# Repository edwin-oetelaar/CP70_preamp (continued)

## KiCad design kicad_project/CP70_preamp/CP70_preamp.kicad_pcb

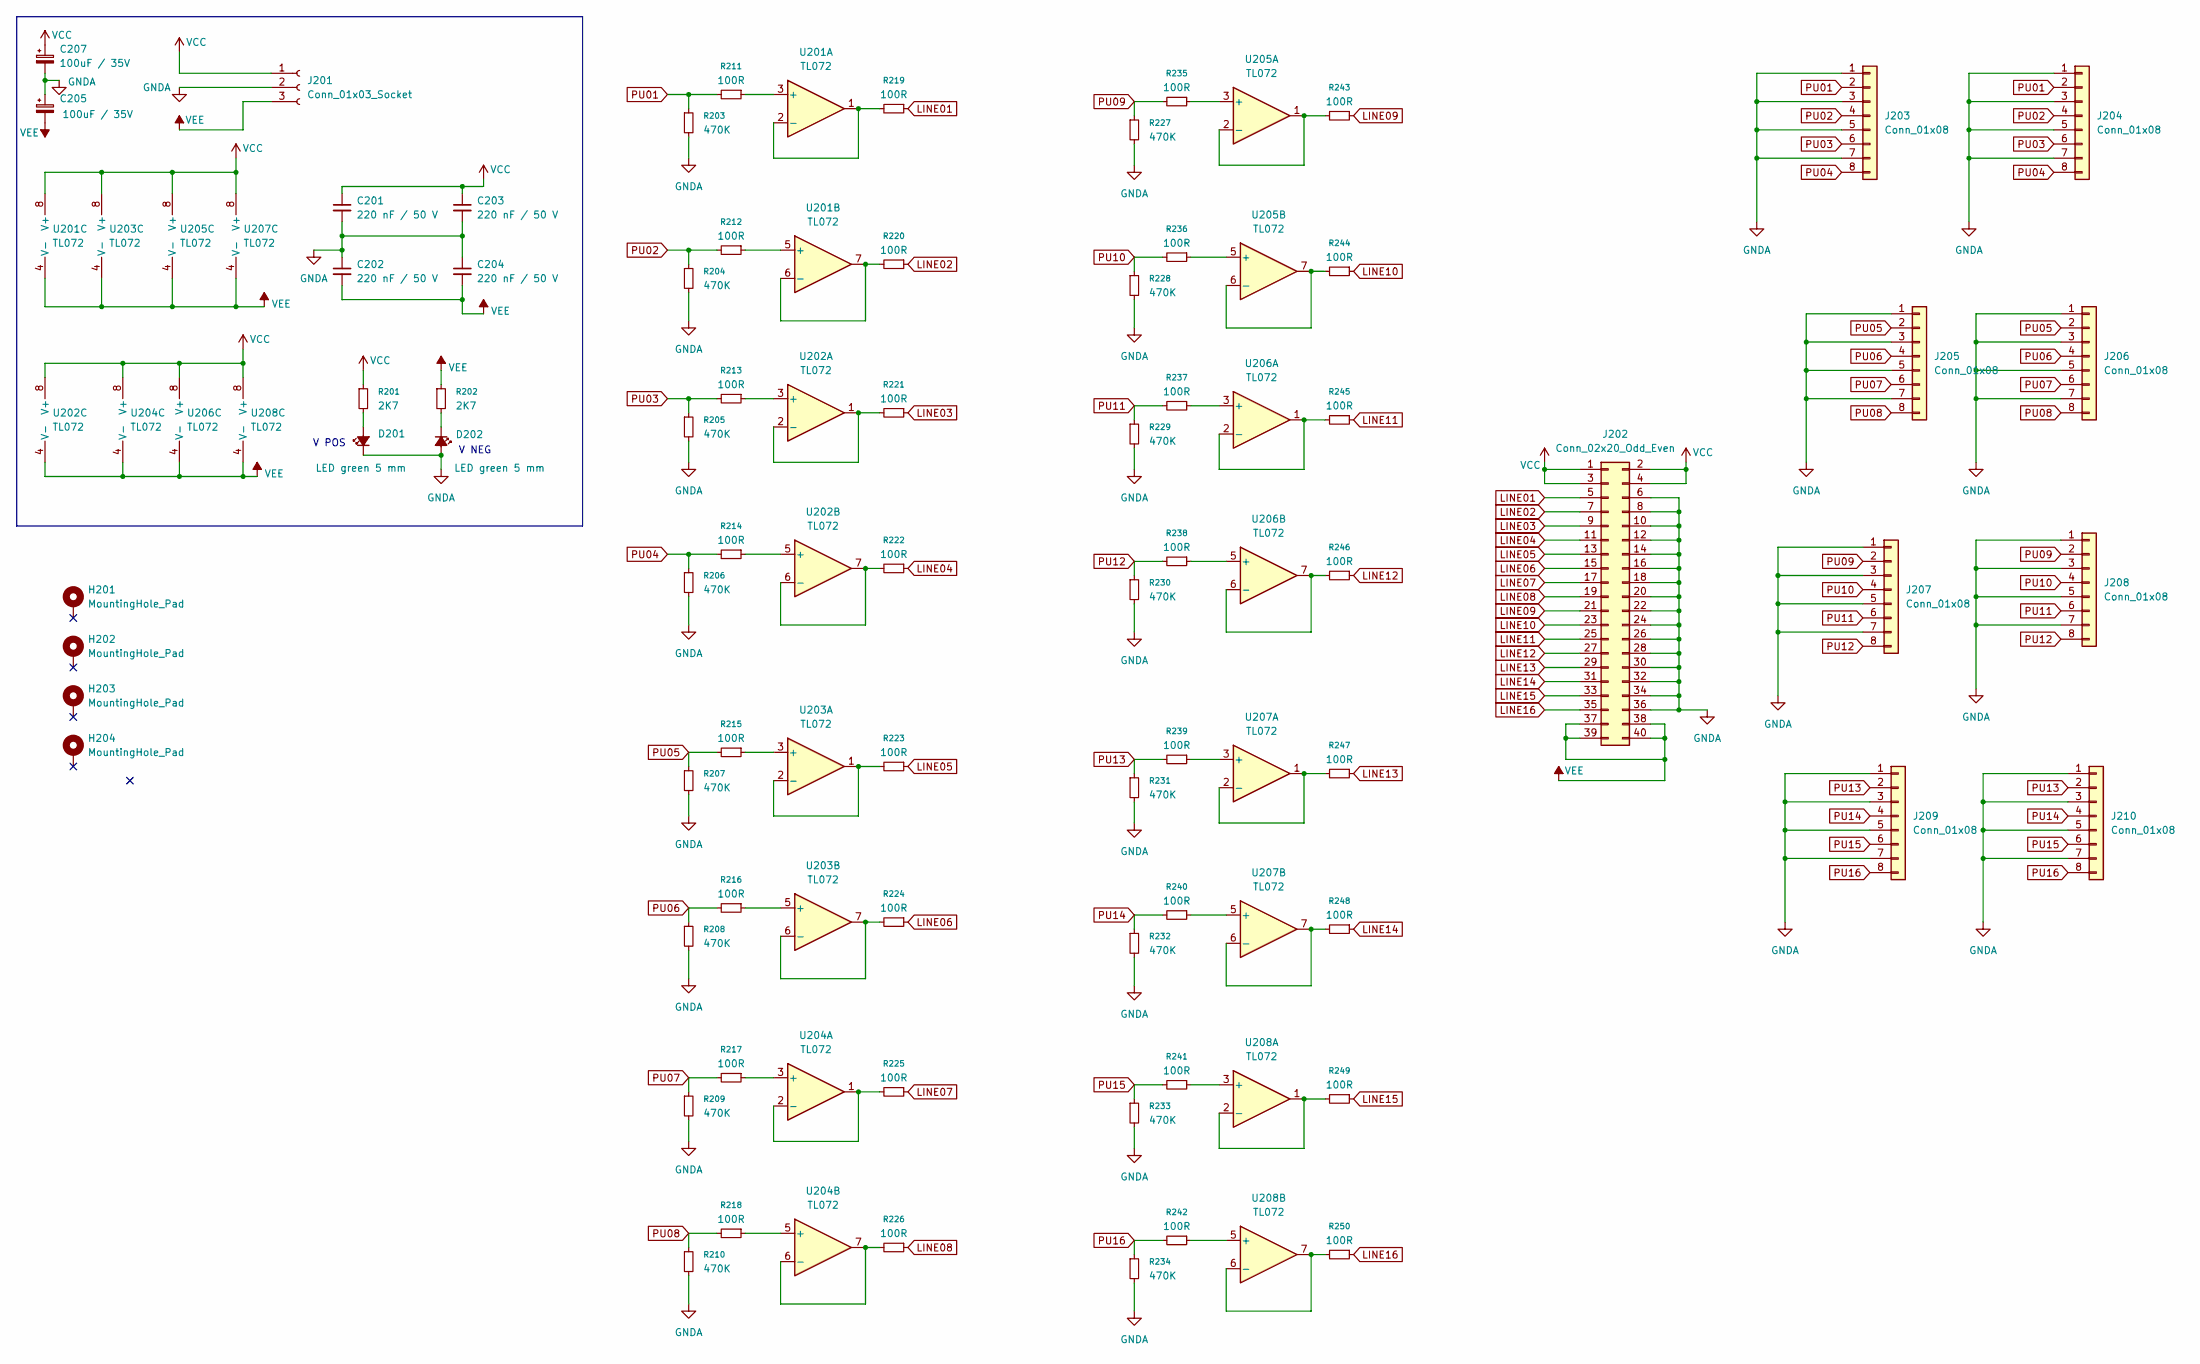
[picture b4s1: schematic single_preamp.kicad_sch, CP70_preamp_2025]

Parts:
C201, C202, C203, C204: 220 nF / 50 V; C_Disc_D6.0mm_W2.5mm_P5.00mm
C205, C207: 100uF / 35V; CP_Radial_D10.0mm_P5.00mm
D201, D202: LED green 5 mm; LED_D5.0mm
H201, H202, H203, H204: MountingHole_Pad; MountingHole_3.2mm_M3_Pad_Via
J201: Conn_01x03_Socket; PhoenixContact_MSTBVA_2,5_3-G-5,08_1x03_P5.08mm_Vertical
J202: Conn_02x20_Odd_Even
J203, J204, J205, J206, J207, J208, J209, J210: Conn_01x08; PinHeader_1x08_P2.54mm_Vertical
R201, R202: 2K7; R_Axial_DIN0207_L6.3mm_D2.5mm_P7.62mm_Horizontal
R203, R204, R205, R206, R207, R208, R209, R210, R227, R228, R229, R230, R231, R232, R233, R234: 470K; R_Axial_DIN0207_L6.3mm_D2.5mm_P7.62mm_Horizontal
R211, R212, R213, R214, R215, R216, R217, R218, R219, R220, R221, R222, R223, R224, R225, R226, R235, R236, R237, R238, R239, R240, R241, R242, R243, R244, R245, R246, R247, R248, R249, R250: 100R; R_Axial_DIN0207_L6.3mm_D2.5mm_P7.62mm_Horizontal
U201, U202, U203, U204, U205, U206, U207, U208: TL072; DIP-8_W7.62mm_LongPads

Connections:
GNDA: C201.2, C202.1, C203.2, C204.1, C205.1, C207.2, D201.1 (K), D202.2 (A), J201.2, J202.6, J202.8, J202.10, J202.12, J202.14, J202.16, J202.18, J202.20, J202.22, J202.24, J202.26, J202.28, J202.30, J202.32, J202.34, J202.36, J203.1, J203.3, J203.5, J203.7, J204.1, J204.3, J204.5, J204.7, J205.1, J205.3, J205.5, J205.7, J206.1, J206.3, J206.5, J206.7, J207.1, J207.3, J207.5, J207.7, J208.1, J208.3, J208.5, J208.7, J209.1, J209.3, J209.5, J209.7, J210.1, J210.3, J210.5, J210.7, R203.2, R204.2, R205.2, R206.2, R207.2, R208.2, R209.2, R210.2, R227.2, R228.2, R229.2, R230.2, R231.2, R232.2, R233.2, R234.2
LINE01: J202.5, R219.1
LINE02: J202.7, R220.1
LINE03: J202.9, R221.1
LINE04: J202.11, R222.1
LINE05: J202.13, R223.1
LINE06: J202.15, R224.1
LINE07: J202.17, R225.1
LINE08: J202.19, R226.1
LINE09: J202.21, R243.1
LINE10: J202.23, R244.1
LINE11: J202.25, R245.1
LINE12: J202.27, R246.1
LINE13: J202.29, R247.1
LINE14: J202.31, R248.1
LINE15: J202.33, R249.1
LINE16: J202.35, R250.1
unnamed: D201.2 (A), R201.2
unnamed: D202.1 (K), R202.2
unnamed: R211.1, U201.3 (+)
unnamed: R219.2, U201.1, U201.2 (-)
unnamed: R212.1, U201.5 (+)
unnamed: R220.2, U201.6 (-), U201.7
unnamed: R213.1, U202.3 (+)
unnamed: R221.2, U202.1, U202.2 (-)
unnamed: R214.1, U202.5 (+)
unnamed: R222.2, U202.6 (-), U202.7
unnamed: R215.1, U203.3 (+)
unnamed: R223.2, U203.1, U203.2 (-)
unnamed: R216.1, U203.5 (+)
unnamed: R224.2, U203.6 (-), U203.7
unnamed: R217.1, U204.3 (+)
unnamed: R225.2, U204.1, U204.2 (-)
unnamed: R218.1, U204.5 (+)
unnamed: R226.2, U204.6 (-), U204.7
unnamed: R235.1, U205.3 (+)
unnamed: R243.2, U205.1, U205.2 (-)
unnamed: R236.1, U205.5 (+)
unnamed: R244.2, U205.6 (-), U205.7
unnamed: R237.1, U206.3 (+)
unnamed: R245.2, U206.1, U206.2 (-)
unnamed: R238.1, U206.5 (+)
unnamed: R246.2, U206.6 (-), U206.7
unnamed: R239.1, U207.3 (+)
unnamed: R247.2, U207.1, U207.2 (-)
unnamed: R240.1, U207.5 (+)
unnamed: R248.2, U207.6 (-), U207.7
unnamed: R241.1, U208.3 (+)
unnamed: R249.2, U208.1, U208.2 (-)
unnamed: R242.1, U208.5 (+)
unnamed: R250.2, U208.6 (-), U208.7
PU01: J203.2, J204.2, R203.1, R211.2
PU02: J203.4, J204.4, R204.1, R212.2
PU03: J203.6, J204.6, R205.1, R213.2
PU04: J203.8, J204.8, R206.1, R214.2
PU05: J205.2, J206.2, R207.1, R215.2
PU06: J205.4, J206.4, R208.1, R216.2
PU07: J205.6, J206.6, R209.1, R217.2
PU08: J205.8, J206.8, R210.1, R218.2
PU09: J207.2, J208.2, R227.1, R235.2
PU10: J207.4, J208.4, R228.1, R236.2
PU11: J207.6, J208.6, R229.1, R237.2
PU12: J207.8, J208.8, R230.1, R238.2
PU13: J209.2, J210.2, R231.1, R239.2
PU14: J209.4, J210.4, R232.1, R240.2
PU15: J209.6, J210.6, R233.1, R241.2
PU16: J209.8, J210.8, R234.1, R242.2
VCC: C201.1, C203.1, C207.1, J201.1, J202.1, J202.2, J202.3, J202.4, R201.1, U201.8 (V+), U202.8 (V+), U203.8 (V+), U204.8 (V+), U205.8 (V+), U206.8 (V+), U207.8 (V+), U208.8 (V+)
VEE: C202.2, C204.2, C205.2, J201.3, J202.37, J202.38, J202.39, J202.40, R202.1, U201.4 (V-), U202.4 (V-), U203.4 (V-), U204.4 (V-), U205.4 (V-), U206.4 (V-), U207.4 (V-), U208.4 (V-)

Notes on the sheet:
V NEG
V POS

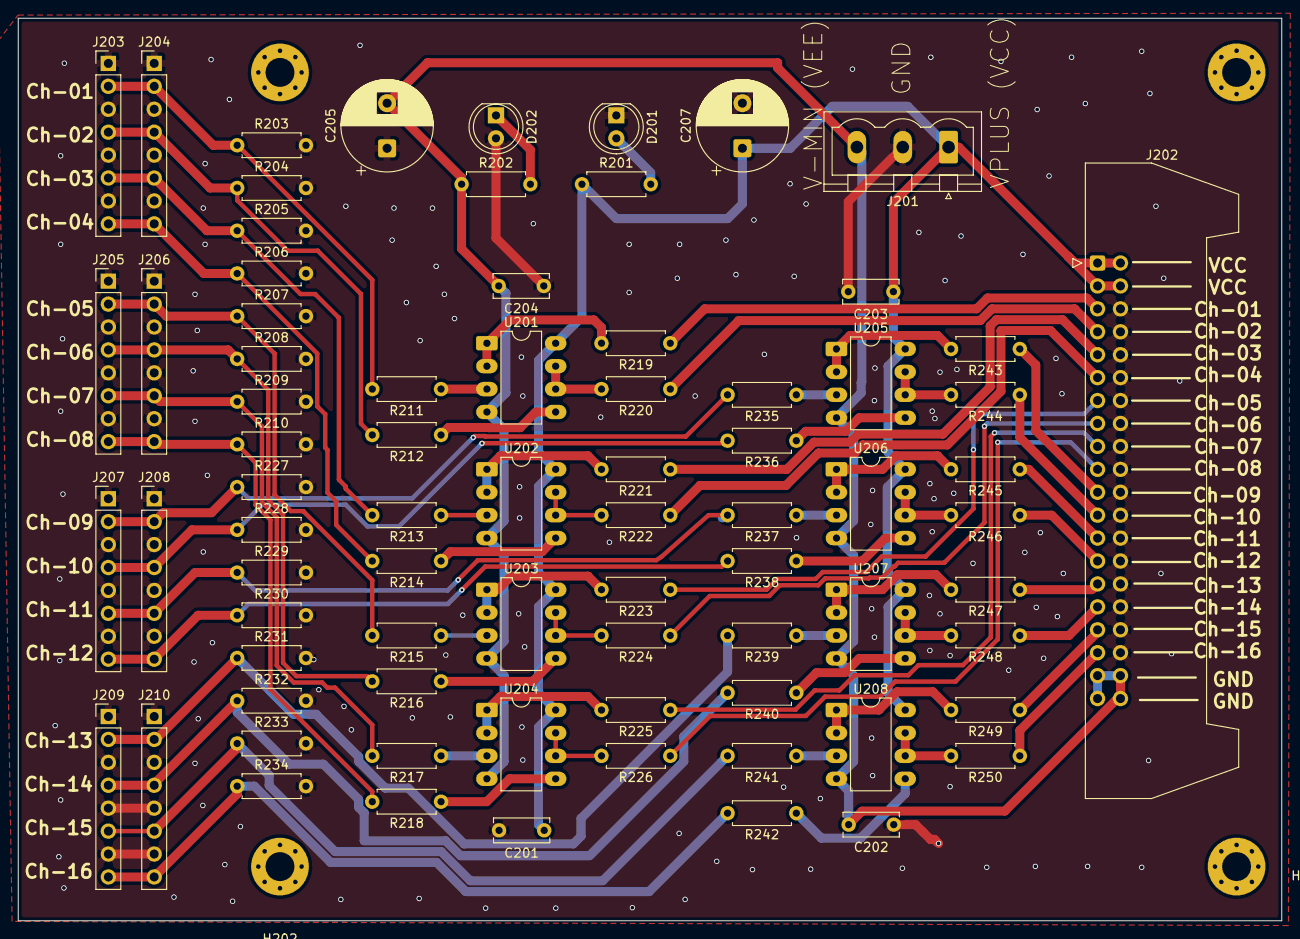
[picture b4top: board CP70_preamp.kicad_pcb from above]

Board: 2 copper layers, 140.0 x 100.0 mm, 80 parts (0 on the bottom side), 69 nets.

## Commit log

2025-05-29 Create README.md
    initial commit
2025-05-29 update info on project
2025-05-29 initial file and directory structure uploaded
2025-05-29 dump of design thoughts and decisions
2025-05-29 design of 16 channel pre amp, including circuit board, ordered. Gerbers in repository.
2025-05-30 Update README.md
    update milestones, parts ordered, pcb ordered and designed
2025-05-30 Update README.md
    location of gerver files corrected
2025-05-30 adding image of CP70B
2025-05-30 adding images of PCB and piano
2025-07-18 Add files via upload
    first set of pre-amp and pot board tested ok
2025-07-18 Update design_decisions.md
    72 channels with spares, total 80 channels built
2025-07-18 adding potmeter board first version
2025-07-18 minor change
2025-08-14 two new boards, needed for breakout of flat cable to power amps and second is flat cable to other flat cable
